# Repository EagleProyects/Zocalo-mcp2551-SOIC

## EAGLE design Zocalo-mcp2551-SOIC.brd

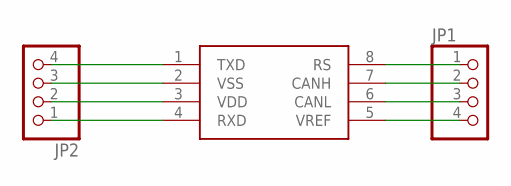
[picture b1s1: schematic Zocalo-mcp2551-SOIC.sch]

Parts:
JP1, JP2: PINHD-1X4; 1X04
U1: MCP2551; SO08

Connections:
unnamed: JP2.4, U1.1 (TXD)
unnamed: JP2.3, U1.2 (VSS)
unnamed: JP2.2, U1.3 (VDD)
unnamed: JP2.1, U1.4 (RXD)
unnamed: JP1.1, U1.8 (RS)
unnamed: JP1.2, U1.7 (CANH)
unnamed: JP1.3, U1.6 (CANL)
unnamed: JP1.4, U1.5 (VREF)

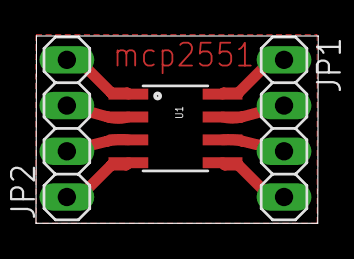
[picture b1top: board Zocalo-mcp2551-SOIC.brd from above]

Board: 2 copper layers, 15.7 x 10.4 mm, 3 parts (0 on the bottom side), 8 nets.

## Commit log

2016-02-28 :circus_tent: Added .gitattributes & .gitignore files

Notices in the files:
parts and their libraries:
SparkFun: Licensing: CC v3.0 Share-Alike You are welcome to use this library for commercial purposes.
